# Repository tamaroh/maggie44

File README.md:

# maggie44

maggie44はTamarohが初めて作成した試作カスタムキーボードです。
- 左右対象、分割、40%、カラムスタッガード
- T、Yキーがホームポジションに近く押しやすい
- 自然にハの字に手が配置される
- 尺屈角度や頻度を減らし手首にやさしいデザイン

## キーマップ

詳細については[ソースコード](https://github.com/tamaroh/qmk_firmware/tree/tamaroh/keyboards/maggie44/keymaps/default)を確認してください

## 必要なもの
|品名|数量|備考|入手先|
|----|----|----|----|
|PCB|2枚|左右別々のデータです<br>ver1.0は一部配線の修正が必要です|このRepositoryのデータから作成してください
|キープレート|2枚|裏返して左右どちらでも使えます|このRepositoryのデータから作成してください
|ボトムプレート大・小|各2枚|アクリル 2mm推奨|このRepositoryのデータから作成してください
|M2ネジ 4mm|20本|ボトムプレートの厚さによって長さは異なります|[遊舎工房](https://shop.yushakobo.jp/products/8006)など
|M2スペーサー 7mm|10個||[遊舎工房](https://shop.yushakobo.jp/products/a0800c2)など
|Pro Micro|2個|すべての互換品については動作を保障しません|[遊舎工房](https://shop.yushakobo.jp/products/pro-micro)など
|ピンヘッダー<br>またはコンスルー|12Pin x 4個||[遊舎工房](https://shop.yushakobo.jp/products/31)など
|タクトスイッチ<br>TS-1136-4.3|2個||[TALP KEYBOARD](https://talpkeyboard.net/items/5fa258a5f0b10814d183347f)など
|ダイオード<br>1N4148|44個|SMD/スルーホール両対応|[TALP KEYBOARD](https://talpkeyboard.net/items/6294480b0ebded1af895c437)など
|スイッチ用PCBソケット|44個|Cherry MX互換のみ対応|[TALP KEYBOARD](https://talpkeyboard.net/items/5e02c5405b120c792616bcf9)など
|TRRSジャック|2個|3.5mm 4極|[TALP KEYBOARD](https://talpkeyboard.net/items/5fa25a06da019c17f0664dc7)など
|TRRSケーブル|1本|TRSでも代用可|[TALP KEYBOARD](https://talpkeyboard.net/items/5e0c0d786c7d63073c5e8845)など
|USBケーブル|1本|Pro MicroとPCを接続できるもの|Amazonなど
|キースイッチ|44個|Cherry MX互換のみ対応|[遊舎工房](https://shop.yushakobo.jp/collections/all-switches)など
|キーキャップ|セット|すべて1Uです|[遊舎工房](https://shop.yushakobo.jp/collections/keycaps)など
|滑り止めゴム足|8個||ダイソーなど

## 必要な工具
- はんだごて
- コテ台、コテ先クリーナー
- はんだ
- 精密ドライバー
- ピンセット

## 制作手順
1. Pro Microにファームウェアを書き込みます。
  QMK Toolboxなどを使用してください。
1. ダイオードを半田付けします。
  SMDの場合縦線が入っている方の端子、スルーホールの場合黒い線がある方の端子を、基板上の縦線がある側に接続してください。

1. Pro Microを用意します。
  コンスルーを使用する場合は基板に仮置きして、適切にPro Microに半田付けしてください。
  
  ピンヘッダを使用する場合は修正が困難なため、向きや表裏を間違えないようにします。
  
  ※USB-Cタイプなどコネクタ部が厚い場合は、ピンヘッダの高さが合わなかったり、コンスルーが抜けやすくなる可能性があります。
1. ソケットを半田付けします。シルク印刷に合わせて、スイッチの穴を塞がないようにします。
  
1. （Ver.1.0の基板のみ）右手用PCBのつながっていない箇所を、銅線などで半田付けしてつなぎます。
  
1. TRRSジャック、リセットスイッチを半田付けします。
  
1. キースイッチを4個程度、先にキープレートに差し込みます。
  
1.  基板と接続します。スイッチのピンが曲がらないように上からまっすぐ抑えます。
2.  残りのスイッチを差し込みます。ソケットとスイッチを指で挟み込むようにして、ソケットに確実に差し込みます。
  
1. キーキャップを取り付けます。
1. ボトムプレートは、プレート大に足となるスペーサーを先に取り付けてから、本体とネジ止めし、最後にプレート小をネジ止めします。

1. プレート大・小にゴム足を取り付けます。
1. できあがり

## ファームウェアについて
ファームウェアは以下にあります。
https://github.com/tamaroh/maggie44/tree/main/firmware
ファイル名|備考
|----|----|
|maggie44_default.hex|VIA有効|
|maggie44_via.json|VIAでキーマップ設定時に使用してください|

ソースコード
https://github.com/tamaroh/qmk_firmware/tree/tamaroh/keyboards/tamaroh/maggie44

## 注意事項
- 非販売品につき、制作に関するサポートはいたしません。
- 試作のため、当レポジトリ内のデータが不完全である可能性があります。

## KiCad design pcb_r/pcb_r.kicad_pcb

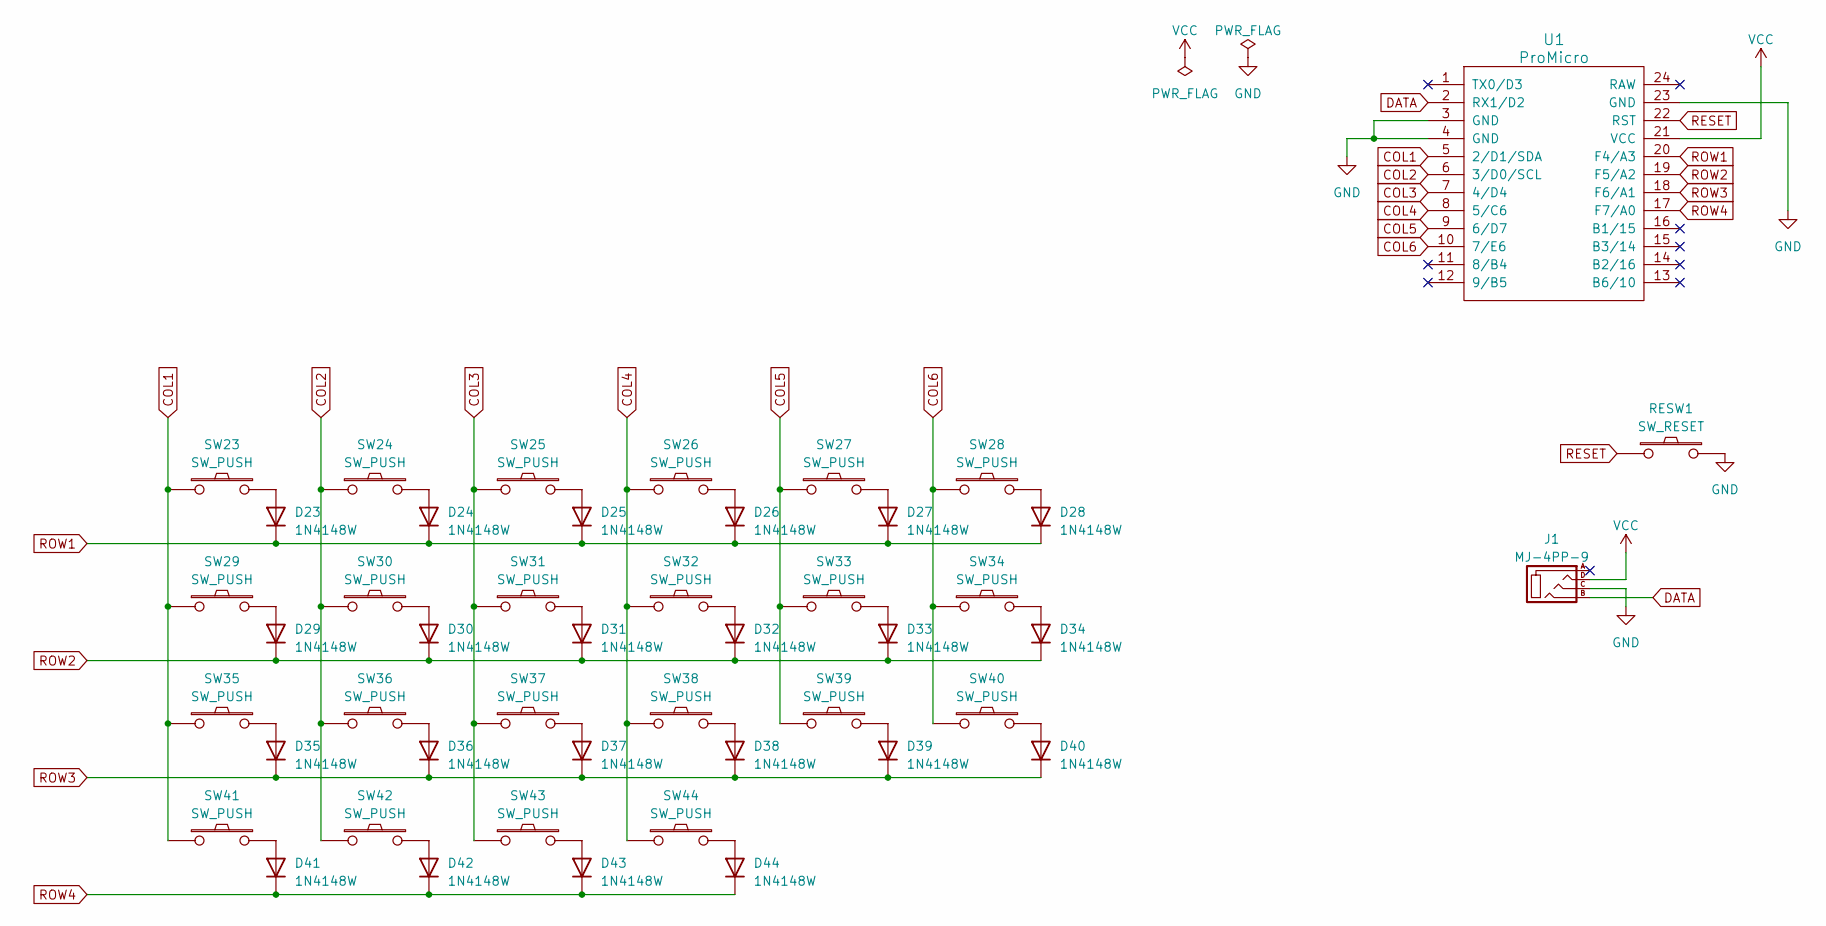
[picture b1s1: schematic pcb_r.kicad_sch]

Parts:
D23, D24, D25, D26, D27, D28, D29, D30, D31, D32, D33, D34, D35, D36, D37, D38, D39, D40, D41, D42, D43, D44: 1N4148W; D3_TH_SMD_v2
J1: MJ-4PP-9; MJ-4PP-9_1side
RESW1: SW_RESET; ResetSW_1side
SW23, SW24, SW25, SW26, SW27, SW28, SW29, SW30, SW31, SW32, SW33, SW34, SW35, SW36, SW37, SW38, SW39, SW40, SW41, SW42, SW43, SW44: SW_PUSH; CherryMX_Hotswap
U1: ProMicro; ProMicro_v3

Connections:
COL1: SW23.1, SW29.1, SW35.1, SW41.1, U1.5 (2/D1/SDA)
COL2: SW24.1, SW30.1, SW36.1, SW42.1, U1.6 (3/D0/SCL)
COL3: SW25.1, SW31.1, SW37.1, SW43.1, U1.7 (4/D4)
COL4: SW26.1, SW32.1, SW38.1, SW44.1, U1.8 (5/C6)
COL5: SW27.1, SW33.1, SW39.1, U1.9 (6/D7)
COL6: SW28.1, SW34.1, SW40.1, U1.10 (7/E6)
DATA: J1.B, U1.2 (RX1/D2)
GND: J1.C, RESW1.2, U1.3 (GND), U1.4 (GND), U1.23 (GND)
unnamed: D23.2 (A), SW23.2
unnamed: D24.2 (A), SW24.2
unnamed: D25.2 (A), SW25.2
unnamed: D26.2 (A), SW26.2
unnamed: D27.2 (A), SW27.2
unnamed: D28.2 (A), SW28.2
unnamed: D29.2 (A), SW29.2
unnamed: D30.2 (A), SW30.2
unnamed: D31.2 (A), SW31.2
unnamed: D32.2 (A), SW32.2
unnamed: D33.2 (A), SW33.2
unnamed: D34.2 (A), SW34.2
unnamed: D35.2 (A), SW35.2
unnamed: D36.2 (A), SW36.2
unnamed: D37.2 (A), SW37.2
unnamed: D38.2 (A), SW38.2
unnamed: D39.2 (A), SW39.2
unnamed: D40.2 (A), SW40.2
unnamed: D41.2 (A), SW41.2
unnamed: D42.2 (A), SW42.2
unnamed: D43.2 (A), SW43.2
unnamed: D44.2 (A), SW44.2
RESET: RESW1.1, U1.22 (RST)
ROW1: D23.1 (K), D24.1 (K), D25.1 (K), D26.1 (K), D27.1 (K), D28.1 (K), U1.20 (F4/A3)
ROW2: D29.1 (K), D30.1 (K), D31.1 (K), D32.1 (K), D33.1 (K), D34.1 (K), U1.19 (F5/A2)
ROW3: D35.1 (K), D36.1 (K), D37.1 (K), D38.1 (K), D39.1 (K), D40.1 (K), U1.18 (F6/A1)
ROW4: D41.1 (K), D42.1 (K), D43.1 (K), D44.1 (K), U1.17 (F7/A0)
VCC: J1.D, U1.21 (VCC)

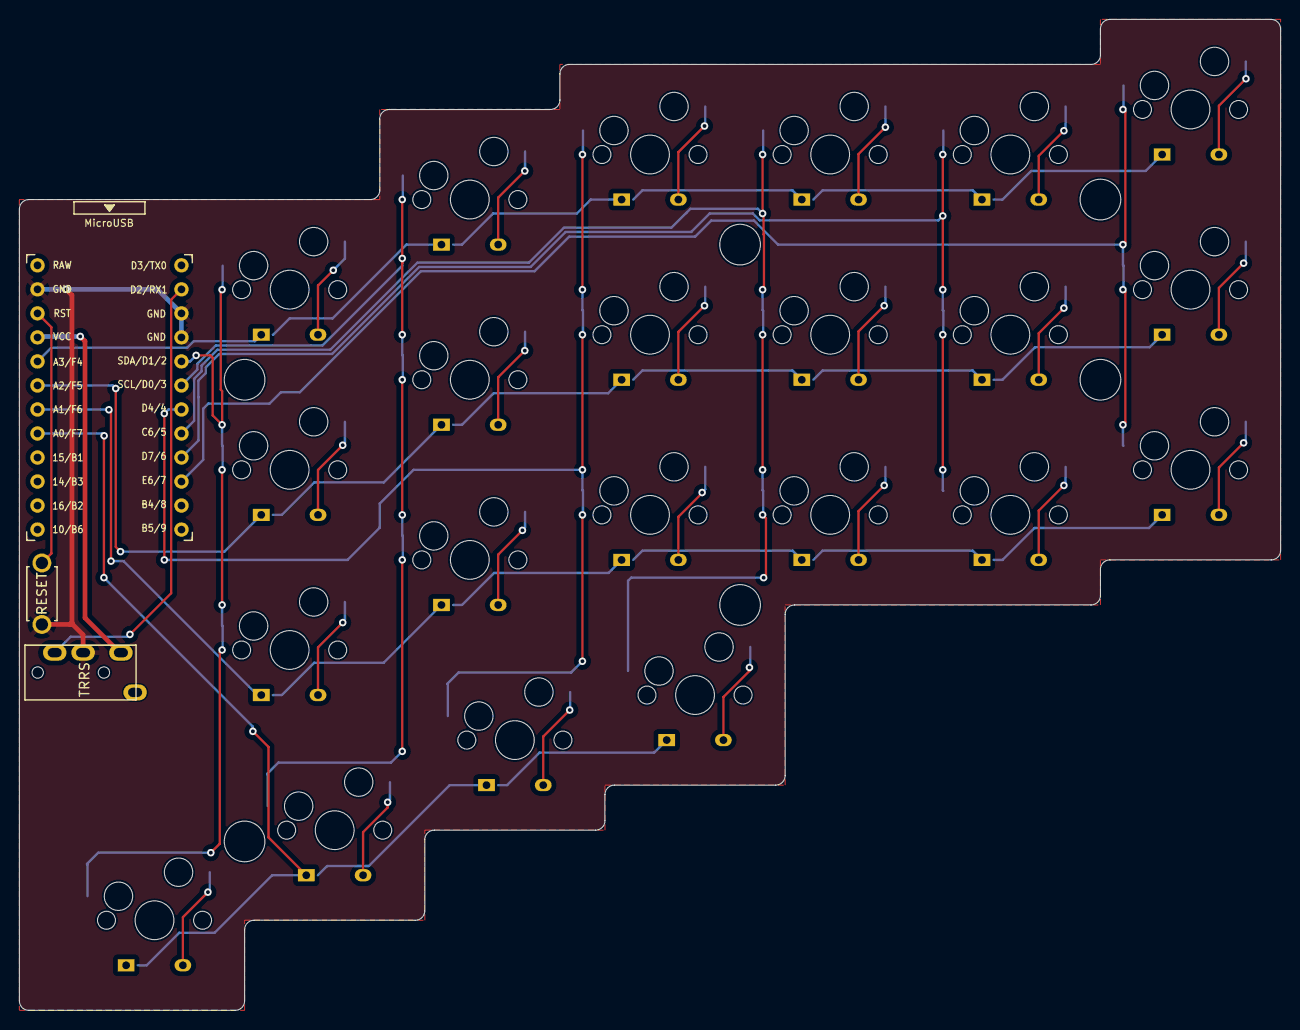
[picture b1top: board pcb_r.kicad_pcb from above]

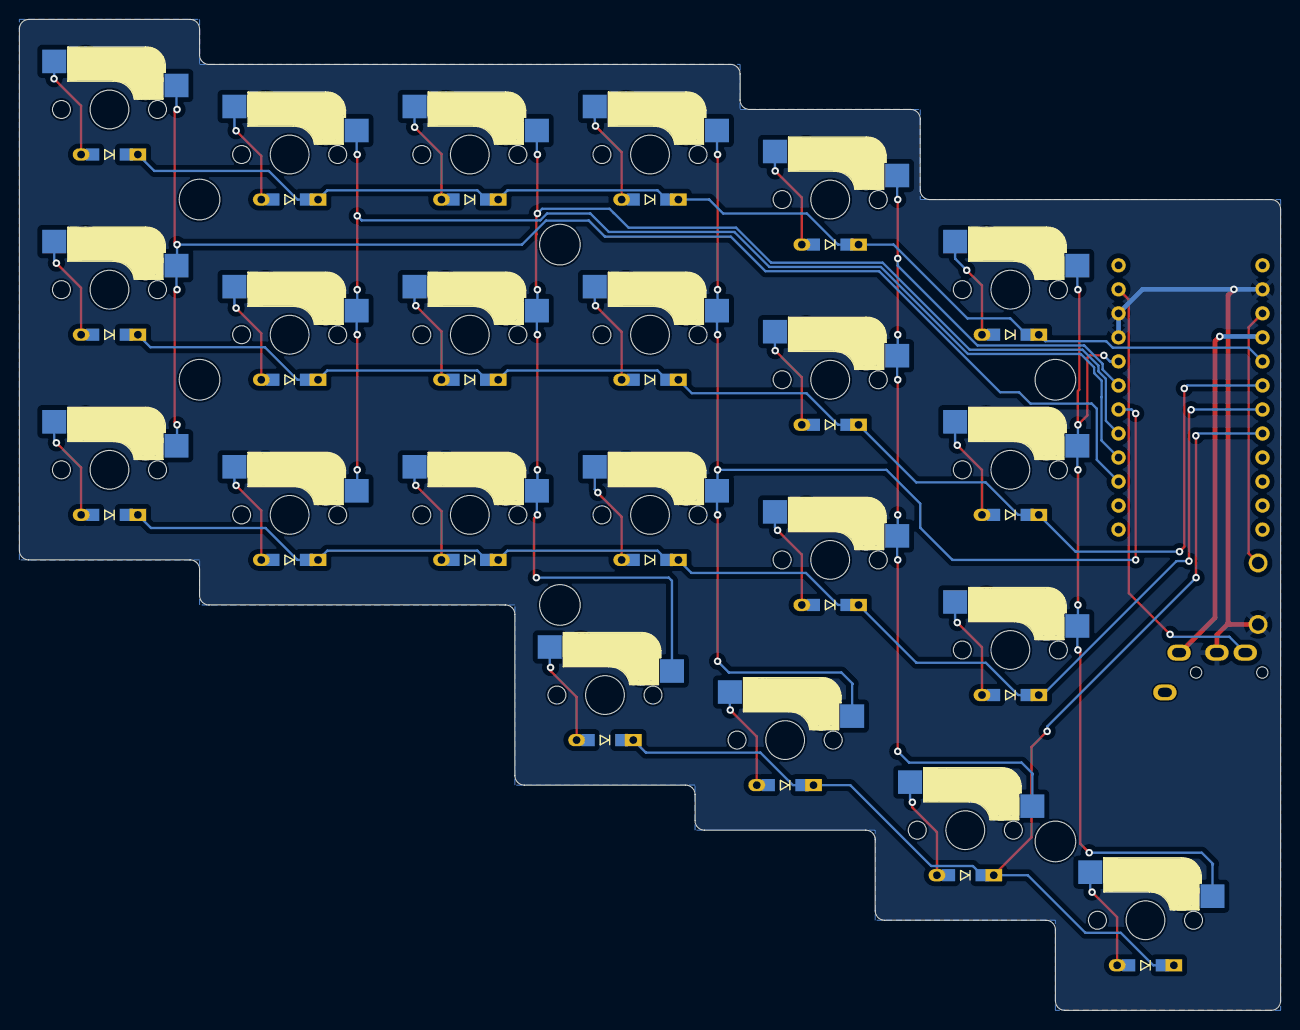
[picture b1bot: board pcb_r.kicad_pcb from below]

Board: 2 copper layers, 133.4 x 104.8 mm, 53 parts (22 on the bottom side), 36 nets.

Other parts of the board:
Ref**: Val**; spacer_m2
Ref**#2, Ref**#3, Ref**#4, Ref**#5, Ref**#6: Val**; spacer_m2

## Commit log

2023-04-11 added submodule from foostan/kbd
2023-04-11 added footprints & libraries
2023-04-16 added keebio pretty submodule
2023-04-16 added keebio setting
2023-04-17 created circuit edit
2023-04-17 layout done
2023-04-23 finished right layout
2023-04-23 fixed folder structure
2023-04-23 added topplate-l, fixed pcb-l hole
2023-04-23 added bottomplate
2023-04-23 added footplate
2023-04-23 added gnd mask
2023-04-23 added plate files
2023-04-23 update svg
2023-05-06 fixed for order
2023-05-06 fixed hole size
2023-05-14 fixed #4
2023-05-14 fixed #6
2023-08-06 created via.json
2023-10-31 added firmware file
2023-10-31 added readme, image is not prepared
2023-10-31 added keymap image
2023-11-03 added images
